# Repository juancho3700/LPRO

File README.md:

# Como programar una placa nRF

1. Instalar la extensión **nRF Connect for VS Code Extension Pack** en Visual Studio Code.
2. Instalar [nRF Command Line Tool](https://www.nordicsemi.com/Products/Development-tools/nRF-Command-Line-Tools/Download).
3. Entrar en el menú de la extensión de nRF (*Ctrl+Alt+N*).
4. Pulsar en el botón *Install Toolchain* y seleccionar la última versión.
5. Pulsar en el botón *Manage SDKs* y seleccionar la última versión.
6. Pulsar en el botón *Open an existing application* y abrir la carpeta **nRFchat**.
7. Conectar la placa que quieras programar al ordenador. Si la extensión la detecta en el submenú *CONNECTED DEVICES* debería aparecer una entrada con un número (el número que está apuntado en la pegatina blanca de la placa).
8. Seleccionar en el submenú *APPLICATIONS* la build respectiva a la placa que estés usando. Si está seleccionada correctamente se pondrá en azul.
9. En el submenú *ACTIONS* pulsar en el botón *build* y en cuanto termine en el botón *flash*.

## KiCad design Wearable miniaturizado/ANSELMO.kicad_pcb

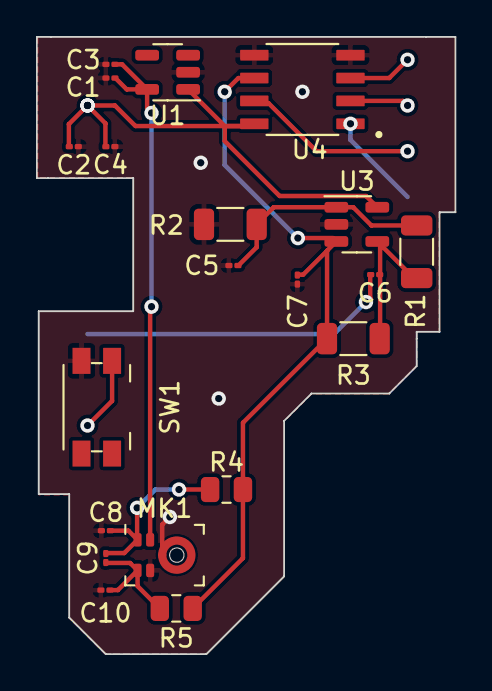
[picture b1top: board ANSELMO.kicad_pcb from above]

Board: 2 copper layers, 23.2 x 34.3 mm, 21 parts (1 on the bottom side), 14 nets.

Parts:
C1, C2, C5, C7: .1uF; C_01005_0402Metric
C3, C4, C6: 10 uF; C_01005_0402Metric
C8, C9, C10: C0402C101KCGACAUTO; C_01005_0402Metric
MK1: IM73A135V01; Infineon_PG-LLGA-5-2
R1, R2, R3: 10k; R_1206_3216Metric
R4, R5: 25k; R_0805_2012Metric
SW1: SW_MEC_5G; Panasonic_EVQPUK_EVQPUB
U1: TLV71330PDBV; SOT-23-5
U2: Pico; RPi_Pico_SMD_TH_MOD
U3: LM321; SOT-23-5
U4: MCP4152-104E_SN; SOIC127P599X175-8N

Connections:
+3.3V: C2.1, C4.2, U1.1 (IN), U2.36 (3V3), U3.5 (V+), U4.8 (VDD)
/3VCC: C1.1, C3.2, MK1.2 (V_{DD}), U1.5 (OUT)
/Vcm: C7.1, R3.1, R4.1, R5.1, U3.3 (-), U4.6 (P0B)
ADC: C6.1, U2.31 (GPIO26_ADC0)
CS*: U2.7 (GPIO5), U4.1 (~CS)
Earth: C1.2, C2.2, C3.1, C4.1, C5.2, C7.2, C8.2, C10.1, MK1.4 (GND), MK1.5 (GND), R2.1, U1.2 (GND), U2.28 (GND), U3.2 (V-), U4.4 (VSS), U4.5 (P0W)
unnamed: C6.2, R1.2, R3.2, U3.4
unnamed: C8.1, C9.2, MK1.1 (OUT+), R4.2
unnamed: C9.1, C10.2, MK1.3 (OUT-), R5.2
unnamed: SW1.1 (A), SW1.2 (A), U2.29 (GPIO22)
unnamed: C5.1, R1.1, R2.2, U3.1 (+)
SCK: U2.4 (GPIO2), U4.3 (SDI)
SDI: U2.5 (GPIO3), U4.2 (SCK)
SDO: U2.6 (GPIO4), U4.7 (SDO)

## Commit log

2024-04-01 Estructura de ficheros
2024-04-01 Añadido nRFchat Explicado en README como programar las placas nRF
2024-04-01 Cambiado nombre de las builds de nRFchat Actualizado README
2024-04-01 Corregido problema al parsear el mensaje
2024-04-02 Solucionados problemas con el serial
2024-04-08 Añadido text to speech y gitignore
2024-04-09 Creado sistema para grabar en wearable
2024-04-09 Implementado STT al Wearable. Añadidos requirements de Python
2024-04-16 Añadido inquiry y peer al wearable (falta implementar y debuggear)
2024-04-17 Implementada comunicacion bluetooth en el wearable
2024-04-25 Cambiado sistema de carpetas
2024-04-30 Codigo terminado (pendiente detalles tontos)
